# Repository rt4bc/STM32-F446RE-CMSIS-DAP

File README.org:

* CMSIS-DAP
Tranplant  a HS USB design from official design, based on STM32-F446RE.
[[file:https://arm-software.github.io/CMSIS_5/DAP/html/CMSIS_DAP_INTERFACE.png]]

* USB Type C
[[file:https://github.com/rt4bc/STM32-F446RE-CMSIS-DAP/blob/main/docs/usb-typec.png]]

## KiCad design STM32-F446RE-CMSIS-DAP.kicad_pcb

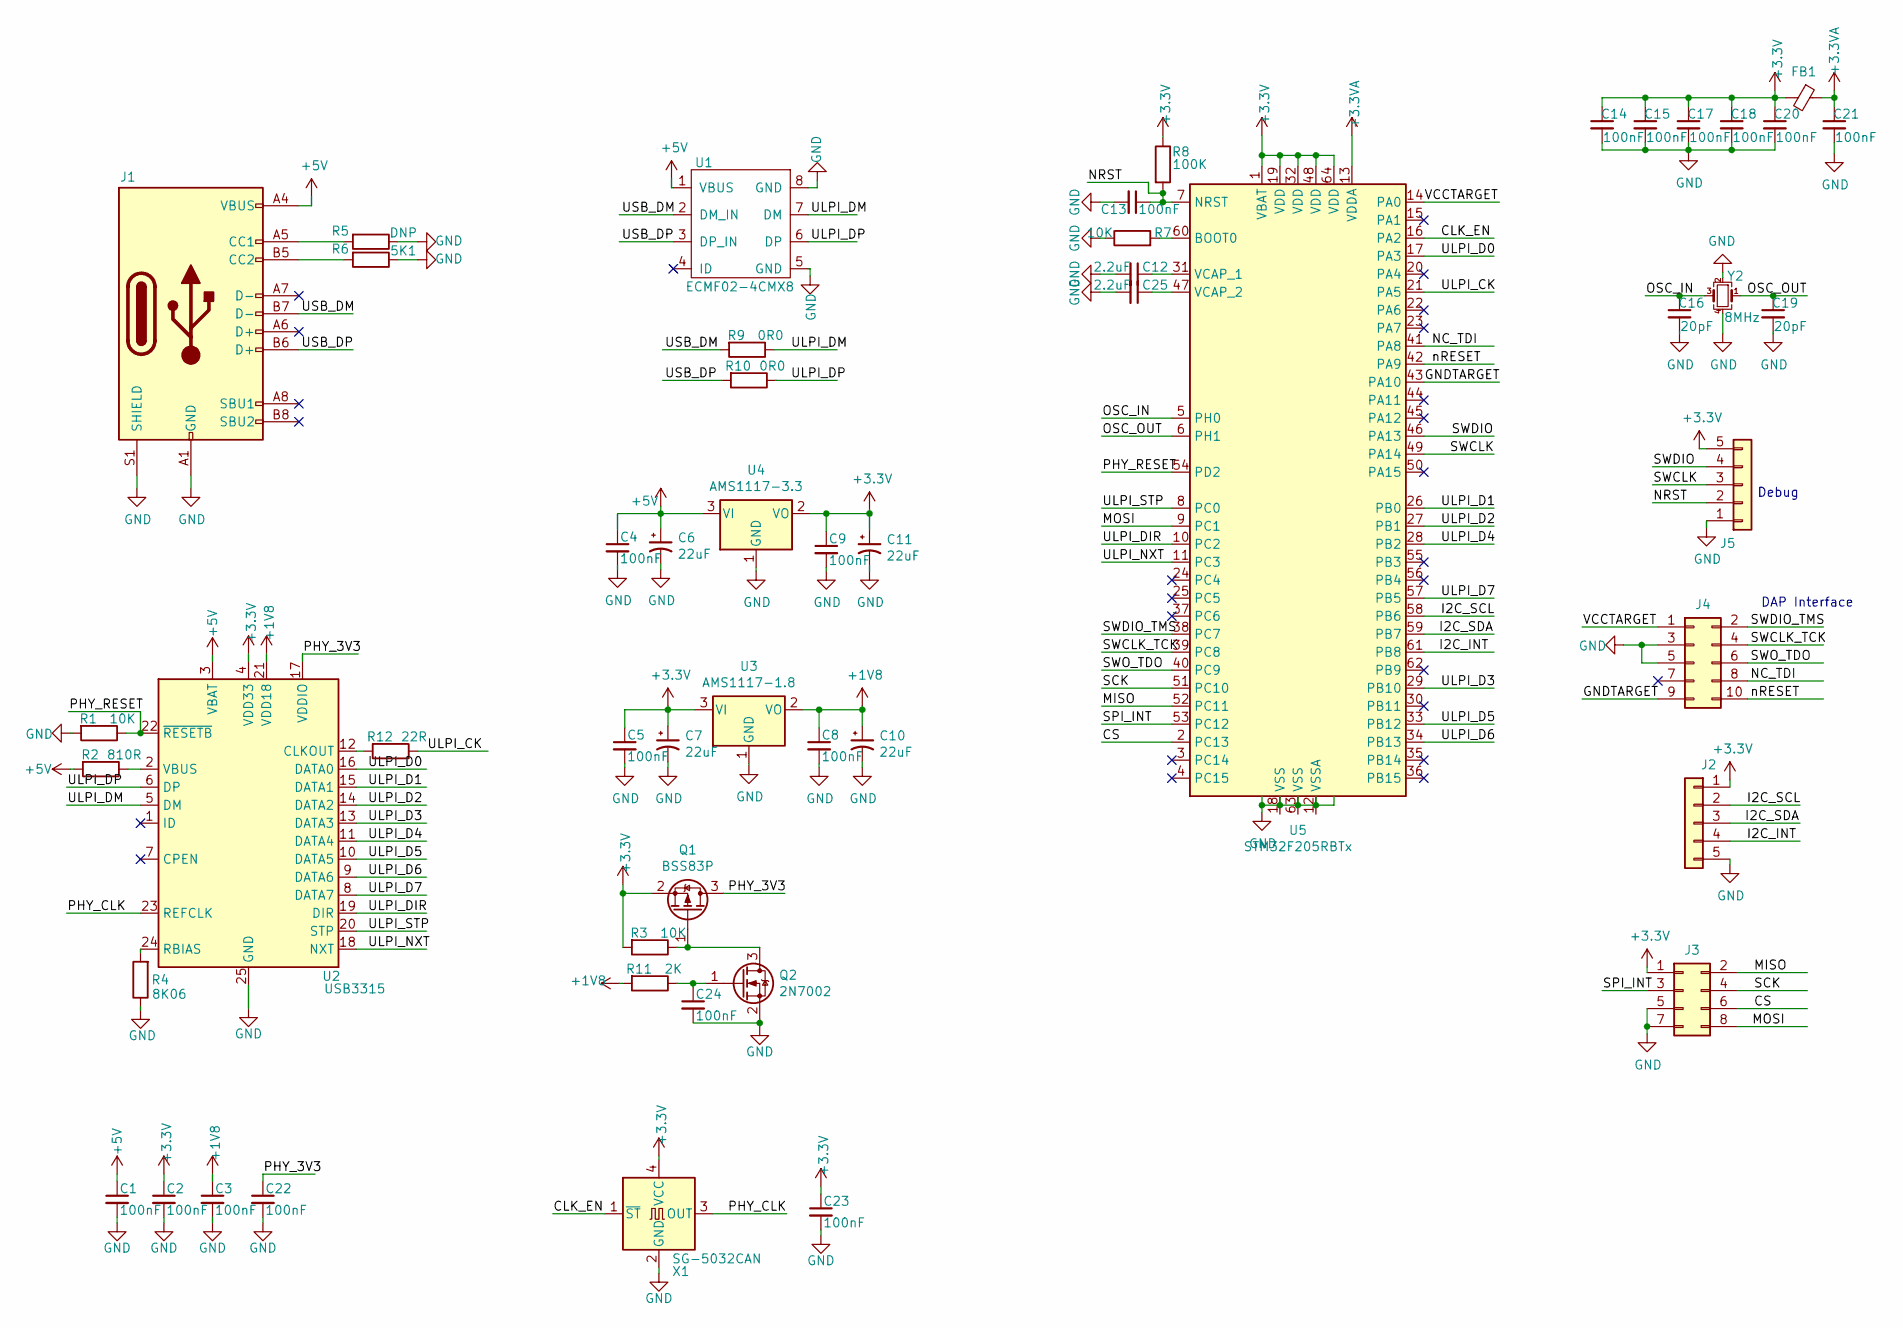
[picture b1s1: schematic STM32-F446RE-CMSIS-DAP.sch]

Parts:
C1, C2, C3, C4, C5, C8, C9, C13, C14, C15, C17, C18, C20, C21, C22, C23, C24: 100nF; C_0603_1608Metric
C6, C7, C10, C11: 22uF; C_0805_2012Metric
C12, C25: 2.2uF; C_0603_1608Metric
C16, C19: 20pF; C_0603_1608Metric
FB1: Ferrite_Bead_Small; L_0603_1608Metric
J1: USB_C_Receptacle_USB2.0; USB_C_Receptacle_HRO_TYPE-C-31-M-12
J2, J5: Conn_01x05; PinHeader_1x05_P2.54mm_Horizontal
J3: Conn_02x04_Odd_Even; PinHeader_2x04_P2.54mm_Horizontal
J4: Conn_02x05_Odd_Even; PinHeader_2x05_P2.54mm_Horizontal
Q1: BSS83P; SOT-23
Q2: 2N7002; SOT-23
R1, R3, R7: 10K; R_0603_1608Metric
R2: 810R; R_0603_1608Metric
R4: 8K06; R_0603_1608Metric
R5: DNP; R_0603_1608Metric
R6: 5K1; R_0603_1608Metric
R8: 100K; R_0603_1608Metric
R9, R10: 0R0; R_0402_1005Metric
R11: 2K; R_0603_1608Metric
R12: 22R; R_0603_1608Metric
U1: ECMF02-4CMX8; Micro_QFN-8_2.5x1.2mm_P0.5mm
U2: USB3315; QFN-24-1EP_4x4mm_P0.5mm_EP2.6x2.6mm
U3: AMS1117-1.8; SOT-223-3_TabPin2
U4: AMS1117-3.3; SOT-223-3_TabPin2
U5: STM32F205RBTx; LQFP-64_10x10mm_P0.5mm
X1: SG-5032CAN; Oscillator_SMD_SeikoEpson_SG8002CE-4Pin_3.2x2.5mm
Y2: 8MHz; Oscillator_SMD_Abracon_ASE-4Pin_3.2x2.5mm

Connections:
+1V8: C3.1, C8.1, C10.1, R11.2, U2.21 (VDD18), U3.2 (VO)
+3.3VA: C21.1, FB1.1, U5.13 (VDDA)
+3V3: C2.1, C5.1, C7.1, C9.1, C11.1, C14.1, C15.1, C17.1, C18.1, C20.1, C23.1, FB1.2, J2.1, J3.1, J5.5, Q1.2 (S), R3.2, R8.1, U2.4 (VDD33), U3.3 (VI), U4.2 (VO), U5.1 (VBAT), U5.19 (VDD), U5.32 (VDD), U5.48 (VDD), U5.64 (VDD), X1.4 (VCC)
+5V: C1.1, C4.1, C6.1, J1.A4 (VBUS), J1.A9 (VBUS), J1.B4 (VBUS), J1.B9 (VBUS), R2.2, U1.1 (VBUS), U2.3 (VBAT), U4.3 (VI)
/CLK_EN: U5.16 (PA2), X1.1 (~ST)
/CS: J3.6, U5.2 (PC13)
/GNDTARGET: J4.9, U5.43 (PA10)
/I2C_INT: J2.4, U5.61 (PB8)
/I2C_SCL: J2.2, U5.58 (PB6)
/I2C_SDA: J2.3, U5.59 (PB7)
/MISO: J3.2, U5.52 (PC11)
/MOSI: J3.8, U5.9 (PC1)
/NC_TDI: J4.8, U5.41 (PA8)
/NRST: C13.1, J5.2, R8.2, U5.7 (NRST)
/OSC_IN: C16.1, U5.5 (PH0), Y2.3
/OSC_OUT: C19.1, U5.6 (PH1), Y2.1
/PHY_3V3: C22.1, Q1.3 (D), U2.17 (VDDIO)
/PHY_CLK: U2.23 (REFCLK), X1.3 (OUT)
/PHY_RESET: R1.1, U2.22 (~RESETB), U5.54 (PD2)
/SCK: J3.4, U5.51 (PC10)
/SPI_INT: J3.3, U5.53 (PC12)
/SWCLK: J5.3, U5.49 (PA14)
/SWCLK_TCK: J4.4, U5.39 (PC8)
/SWDIO: J5.4, U5.46 (PA13)
/SWDIO_TMS: J4.2, U5.38 (PC7)
/SWO_TDO: J4.6, U5.40 (PC9)
/ULPI_CK: R12.1, U5.21 (PA5)
/ULPI_D0: U2.16 (DATA0), U5.17 (PA3)
/ULPI_D1: U2.15 (DATA1), U5.26 (PB0)
/ULPI_D2: U2.14 (DATA2), U5.27 (PB1)
/ULPI_D3: U2.13 (DATA3), U5.29 (PB10)
/ULPI_D4: U2.11 (DATA4), U5.28 (PB2)
/ULPI_D5: U2.10 (DATA5), U5.33 (PB12)
/ULPI_D6: U2.9 (DATA6), U5.34 (PB13)
/ULPI_D7: U2.8 (DATA7), U5.57 (PB5)
/ULPI_DIR: U2.19 (DIR), U5.10 (PC2)
/ULPI_DM: R9.1, U1.7 (DM), U2.5 (DM)
/ULPI_DP: R10.1, U1.6 (DP), U2.6 (DP)
/ULPI_NXT: U2.18 (NXT), U5.11 (PC3)
/ULPI_STP: U2.20 (STP), U5.8 (PC0)
/USB_DM: J1.B7 (D-), R9.2, U1.2 (DM_IN)
/USB_DP: J1.B6 (D+), R10.2, U1.3 (DP_IN)
/VCCTARGET: J4.1, U5.14 (PA0)
/nRESET: J4.10, U5.42 (PA9)
GND: C1.2, C2.2, C3.2, C4.2, C5.2, C6.2, C7.2, C8.2, C9.2, C10.2, C11.2, C12.2, C13.2, C14.2, C15.2, C16.2, C17.2, C18.2, C19.2, C20.2, C21.2, C22.2, C23.2, C24.2, C25.2, J1.A1 (GND), J1.A12 (GND), J1.B1 (GND), J1.B12 (GND), J1.S1 (SHIELD), J2.5, J3.5, J3.7, J4.3, J4.5, J5.1, Q2.2 (S), R1.2, R4.1, R5.1, R6.1, R7.1, U1.5 (GND), U1.8 (GND), U2.25 (GND), U3.1 (GND), U4.1 (GND), X1.2 (GND), Y2.2, Y2.4
unnamed: C12.1, U5.31 (VCAP_1)
unnamed: C24.1, Q2.1 (G), R11.1
unnamed: C25.1, U5.47 (VCAP_2)
unnamed: J1.A5 (CC1), R5.2
unnamed: J1.B5 (CC2), R6.2
unnamed: Q1.1 (G), Q2.3 (D), R3.1
unnamed: R2.1, U2.2 (VBUS)
unnamed: R4.2, U2.24 (RBIAS)
unnamed: R7.2, U5.60 (BOOT0)
unnamed: R12.2, U2.12 (CLKOUT)

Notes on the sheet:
Debug
DAP Interface

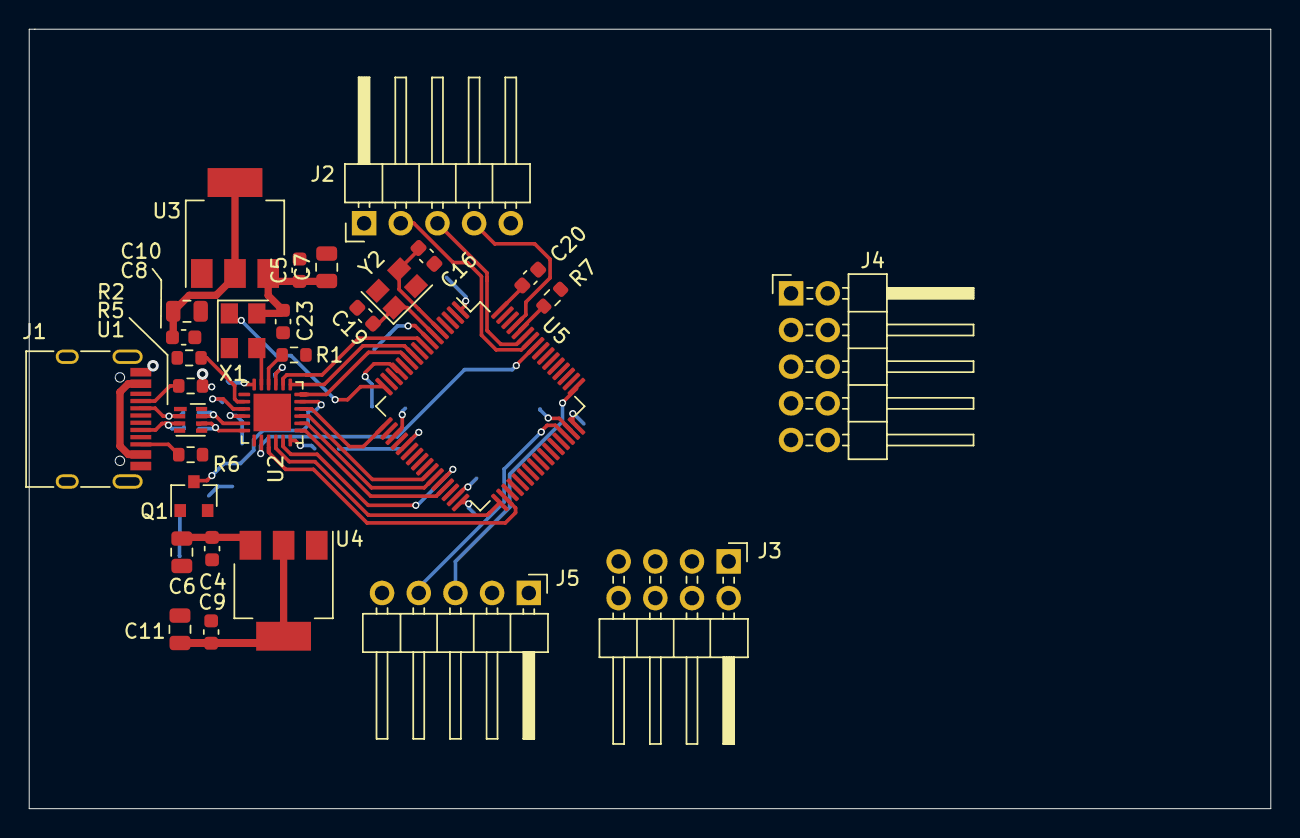
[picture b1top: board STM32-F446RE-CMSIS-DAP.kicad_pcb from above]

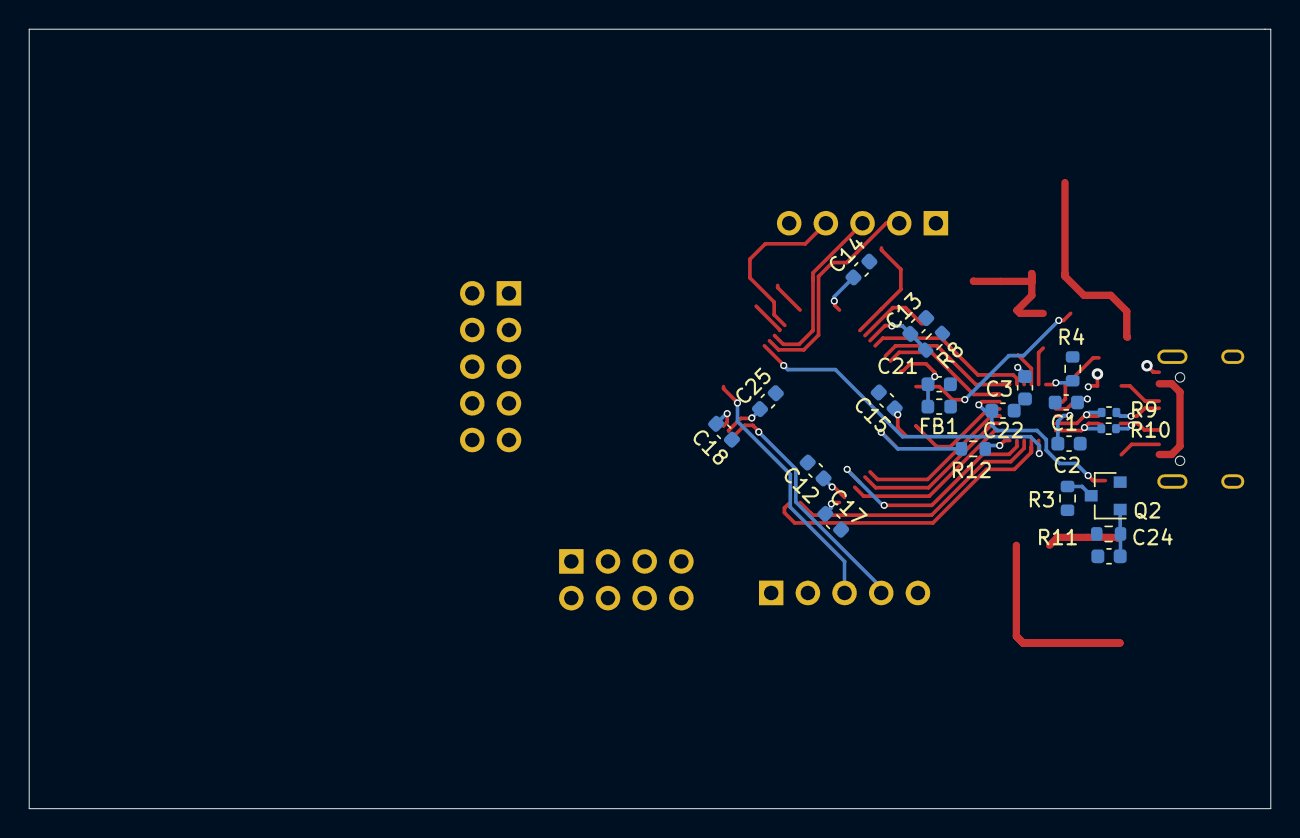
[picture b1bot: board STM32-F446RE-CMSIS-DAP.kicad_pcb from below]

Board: 2 copper layers, 86.0 x 54.0 mm, 52 parts (22 on the bottom side), 55 nets.

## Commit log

2021-03-16 add design files
2021-03-16 add readme.org
2021-03-16 inline cmsis-dap images
2021-03-16 add usb type c pinout image
2021-03-17 update schematic
2021-04-20 Route usb ulpi
2021-04-20 update route
